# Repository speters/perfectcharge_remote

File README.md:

# perfectcharge_remote
Reverse engineering of the Waeco PerfectCharge remote controller.

The remote controller for the Waeco PerfectCharge line of marine battery chargers is a really simple device consisting of no more than a pushbutton switch and some leds.

PCB is single layer with two jumper wires on top side.

Schematic and PCB as been recreated in KiCAD:

KiCAD design files and manufacturing files (Gerber, Excellon drill) can be found in repository.

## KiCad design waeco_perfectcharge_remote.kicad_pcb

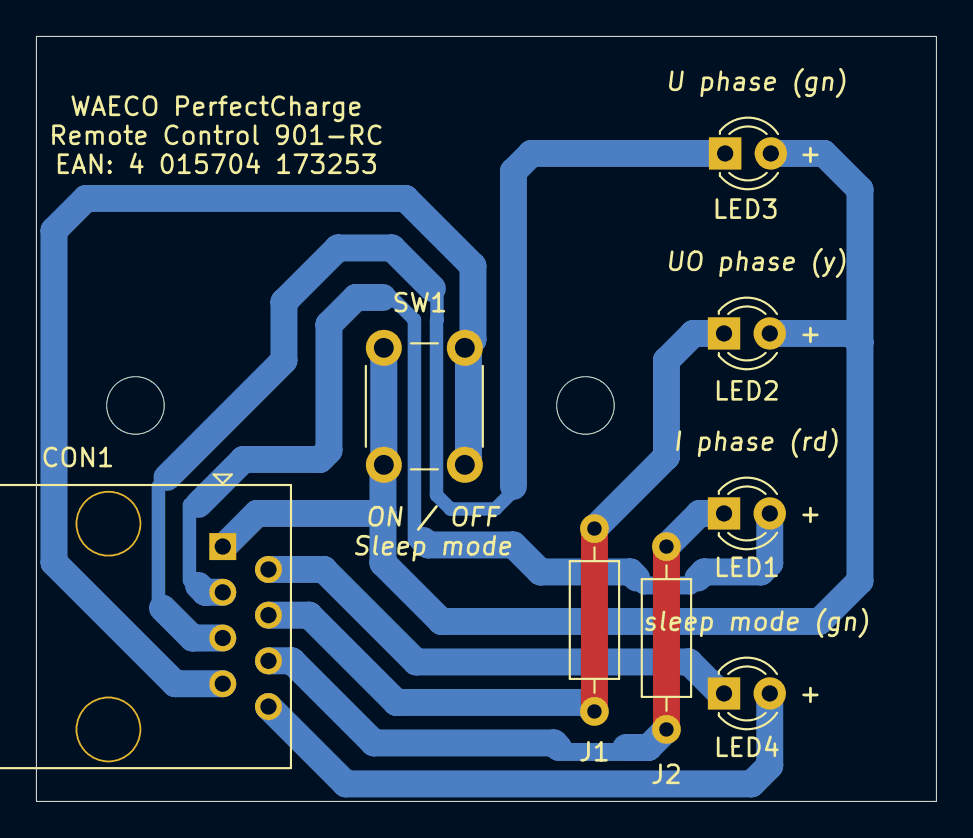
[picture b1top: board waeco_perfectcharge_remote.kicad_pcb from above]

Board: 2 copper layers, 50.0 x 42.5 mm, 10 parts (0 on the bottom side), 8 nets.

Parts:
CON1: RJ45; RJ45_OST_PJ012-8P8CX_Vertical
H1, H2: MountingHole; MountingHole_3.2mm_M3
J1, J2: Jumper; R_Axial_DIN0207_L6.3mm_D2.5mm_P10.16mm_Horizontal
LED1: red 3mm; LED_D3.0mm
LED2: yellow 3mm; LED_D3.0mm
LED3, LED4: green 3mm; LED_D3.0mm
SW1: SW_Push; SW_PUSH_6mm_H13mm

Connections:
unnamed: CON1.1, LED2.2, LED3.2, SW1.1
unnamed: CON1.2, LED4.1
unnamed: CON1.3, LED1.2
unnamed: CON1.4, J1.1, J1.2, LED2.1
unnamed: CON1.5, LED3.1
unnamed: CON1.6, J2.1, J2.2, LED1.1
unnamed: CON1.7, SW1.2
unnamed: CON1.8, LED4.2

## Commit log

2021-08-30 KiCAD files
2021-08-31 rounded tracks
